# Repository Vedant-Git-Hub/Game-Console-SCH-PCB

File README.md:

# Game-Console-SCH-PCB
This repository consist of schematics and PCB for the game console hardware. THis project is designed and developed in KICAD-5.

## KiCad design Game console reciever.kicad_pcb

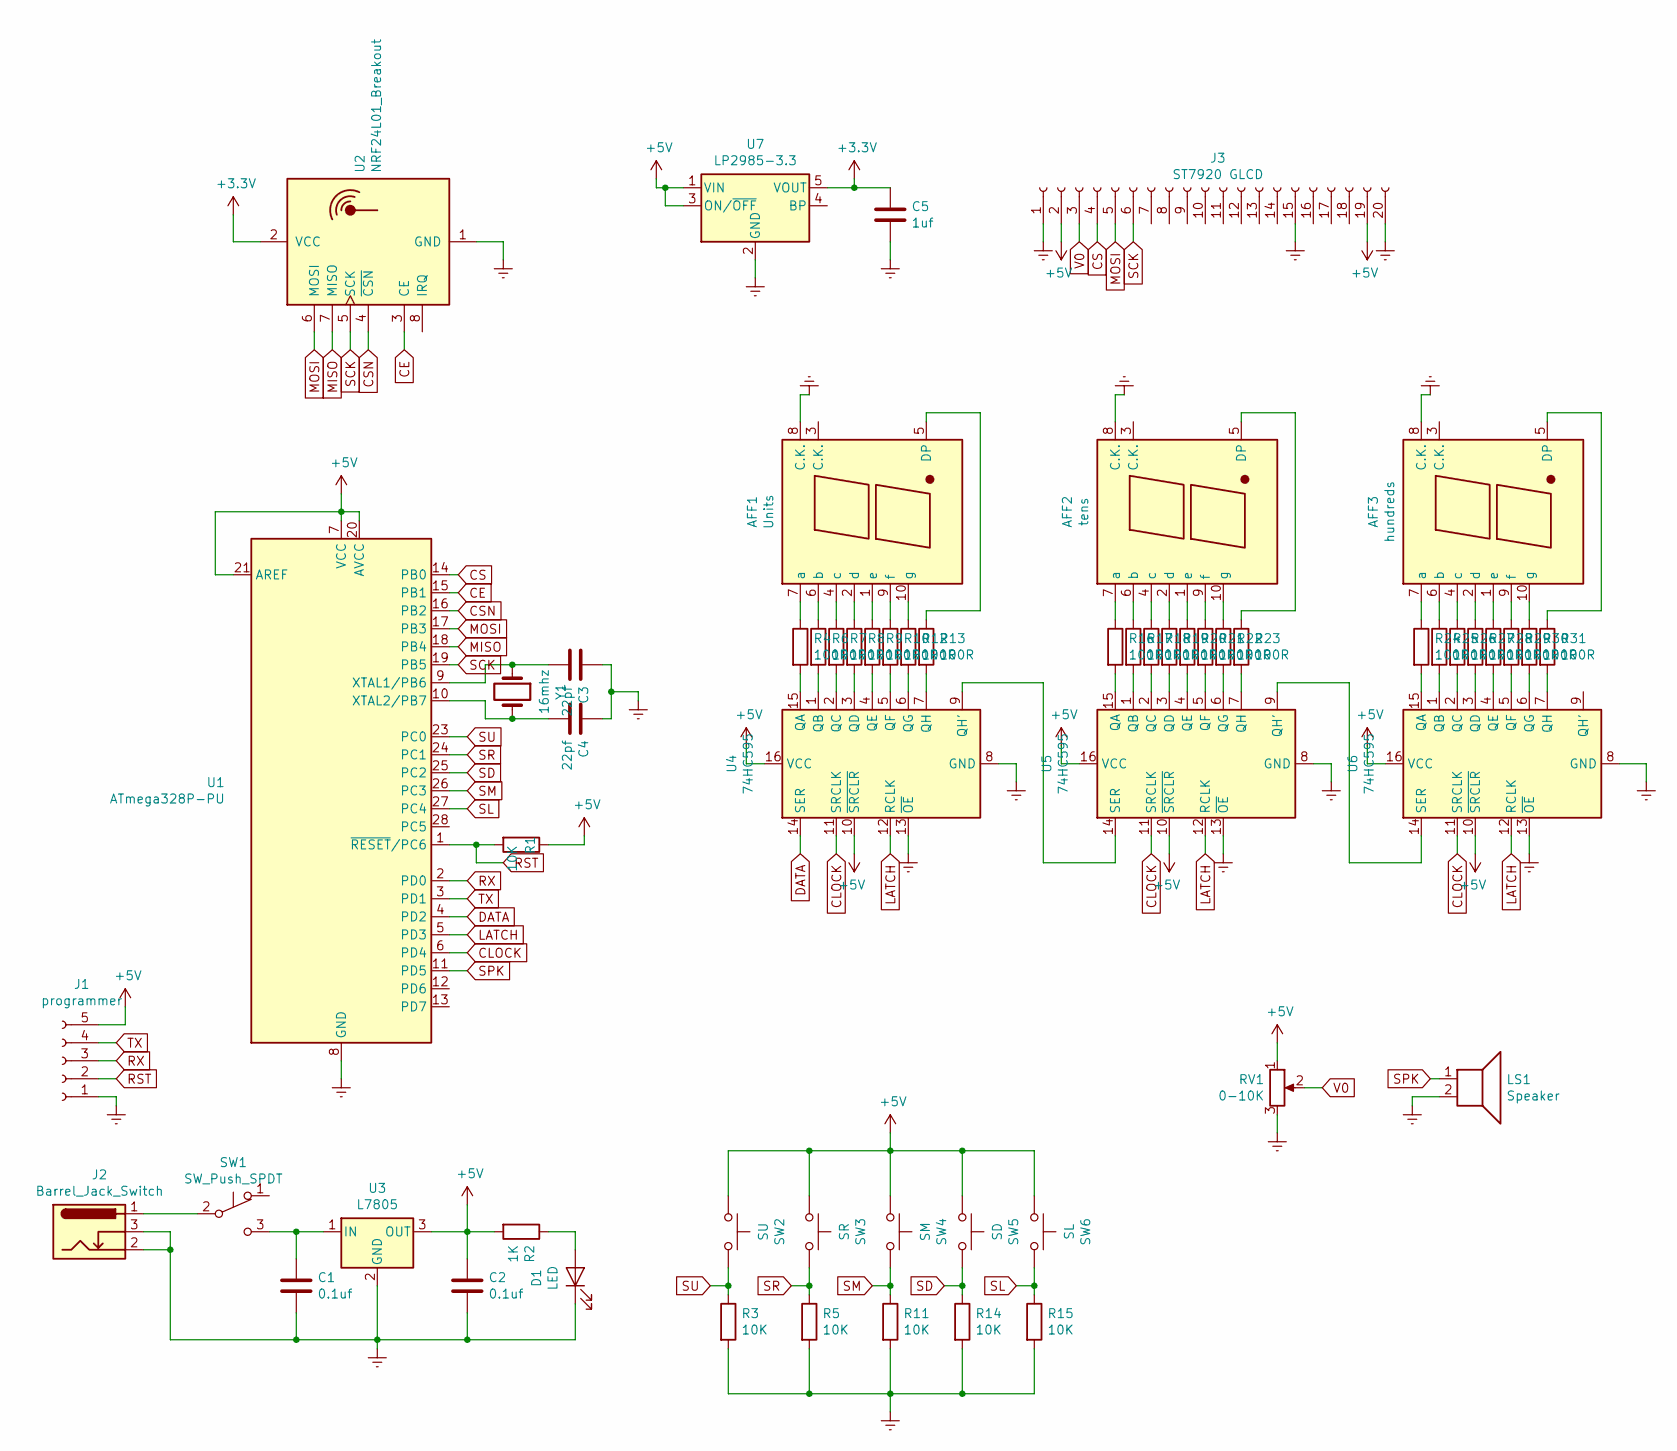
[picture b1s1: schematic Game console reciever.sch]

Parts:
AFF1: Units; 7SegmentLED_LTS6760_LTS6780
AFF2: tens; 7SegmentLED_LTS6760_LTS6780
AFF3: hundreds; 7SegmentLED_LTS6760_LTS6780
C1, C2: 0.1uf; C_Disc_D5.0mm_W2.5mm_P5.00mm
C3, C4: 22pf; C_Disc_D5.0mm_W2.5mm_P5.00mm
C5: 1uf; C_Disc_D5.0mm_W2.5mm_P5.00mm
D1: LED; LED_D5.0mm
J1: programmer; PinHeader_1x05_P2.54mm_Vertical
J2: Barrel_Jack_Switch; BarrelJack_Wuerth_6941xx301002
J3: ST7920 GLCD; PinHeader_1x20_P2.54mm_Vertical
LS1: Speaker; PinHeader_1x02_P2.54mm_Vertical
R1, R3, R5, R11, R14, R15: 10K; R_Axial_DIN0207_L6.3mm_D2.5mm_P10.16mm_Horizontal
R2: 1K; R_Axial_DIN0207_L6.3mm_D2.5mm_P10.16mm_Horizontal
R4, R6, R7, R8, R9, R10, R12, R13, R16, R17, R18, R19, R20, R21, R22, R23, R24, R25, R26, R27, R28, R29, R30, R31: 100R; R_Axial_DIN0207_L6.3mm_D2.5mm_P10.16mm_Horizontal
RV1: 0-10K; Potentiometer_Bourns_3266Z_Horizontal
SW1: SW_Push_SPDT; PinHeader_1x03_P2.00mm_Vertical
SW2: SU; TE_FSM8JRT
SW3: SR; TE_FSM8JRT
SW4: SM; TE_FSM8JRT
SW5: SD; TE_FSM8JRT
SW6: SL; TE_FSM8JRT
U1: ATmega328P-PU; DIP-28_W7.62mm
U2: NRF24L01_Breakout; nRF24L01_Breakout
U3: L7805; TO254P460X1020X1945-3P
U4, U5, U6: 74HC595; DIP-16_W7.62mm_LongPads
U7: LP2985-3.3; SOT-23-5
Y1: 16mhz; Crystal_HC52-6mm_Vertical

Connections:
+3V3: C5.1, U2.2 (VCC), U7.5 (VOUT)
+5V: C2.1, J1.5, J3.2, J3.19, R1.1, R2.2, RV1.1, SW2.1, SW3.1, SW4.1, SW5.1, SW6.1, U1.7 (VCC), U1.20 (AVCC), U1.21 (AREF), U3.3 (OUT), U4.10 (~SRCLR), U4.16 (VCC), U5.10 (~SRCLR), U5.16 (VCC), U6.10 (~SRCLR), U6.16 (VCC), U7.1 (VIN), U7.3 (ON/~OFF~)
CE: U1.15 (PB1), U2.3 (CE)
CLOCK: U1.6 (PD4), U4.11 (SRCLK), U5.11 (SRCLK), U6.11 (SRCLK)
CS: J3.4, U1.14 (PB0)
CSN: U1.16 (PB2), U2.4 (~CSN)
DATA: U1.4 (PD2), U4.14 (SER)
Earth: AFF1.8 (C.K.), AFF2.8 (C.K.), AFF3.8 (C.K.), C1.2, C2.2, C3.1, C4.1, C5.2, D1.1 (K), J1.1, J2.2, J2.3, J3.1, J3.15, J3.20, LS1.2, R3.2, R5.2, R11.2, R14.2, R15.2, RV1.3, U1.8 (GND), U1.22 (GND), U2.1 (GND), U3.2 (GND), U4.8 (GND), U4.13 (~OE), U5.8 (GND), U5.13 (~OE), U6.8 (GND), U6.13 (~OE), U7.2 (GND)
LATCH: U1.5 (PD3), U4.12 (RCLK), U5.12 (RCLK), U6.12 (RCLK)
MISO: U1.18 (PB4), U2.7 (MISO)
MOSI: J3.5, U1.17 (PB3), U2.6 (MOSI)
unnamed: AFF1.1 (e), R9.1
unnamed: AFF1.2 (d), R8.1
unnamed: AFF1.4 (c), R7.1
unnamed: AFF1.5 (DP), R13.1
unnamed: AFF1.6 (b), R6.1
unnamed: AFF1.7 (a), R4.1
unnamed: AFF1.9 (f), R10.1
unnamed: AFF1.10 (g), R12.1
unnamed: AFF2.1 (e), R20.1
unnamed: AFF2.2 (d), R19.1
unnamed: AFF2.4 (c), R18.1
unnamed: AFF2.5 (DP), R23.1
unnamed: AFF2.6 (b), R17.1
unnamed: AFF2.7 (a), R16.1
unnamed: AFF2.9 (f), R21.1
unnamed: AFF2.10 (g), R22.1
unnamed: AFF3.1 (e), R28.1
unnamed: AFF3.2 (d), R27.1
unnamed: AFF3.4 (c), R26.1
unnamed: AFF3.5 (DP), R31.1
unnamed: AFF3.6 (b), R25.1
unnamed: AFF3.7 (a), R24.1
unnamed: AFF3.9 (f), R29.1
unnamed: AFF3.10 (g), R30.1
unnamed: C1.1, SW1.3 (C), U3.1 (IN)
unnamed: C3.2, U1.9 (XTAL1/PB6), Y1.1
unnamed: C4.2, U1.10 (XTAL2/PB7), Y1.2
unnamed: D1.2 (A), R2.1
unnamed: J2.1, SW1.2 (B)
unnamed: R4.2, U4.15 (QA)
unnamed: R6.2, U4.1 (QB)
unnamed: R7.2, U4.2 (QC)
unnamed: R8.2, U4.3 (QD)
unnamed: R9.2, U4.4 (QE)
unnamed: R10.2, U4.5 (QF)
unnamed: R12.2, U4.6 (QG)
unnamed: R13.2, U4.7 (QH)
unnamed: R16.2, U5.15 (QA)
unnamed: R17.2, U5.1 (QB)
unnamed: R18.2, U5.2 (QC)
unnamed: R19.2, U5.3 (QD)
unnamed: R20.2, U5.4 (QE)
unnamed: R21.2, U5.5 (QF)
unnamed: R22.2, U5.6 (QG)
unnamed: R23.2, U5.7 (QH)
unnamed: R24.2, U6.15 (QA)
unnamed: R25.2, U6.1 (QB)
unnamed: R26.2, U6.2 (QC)
unnamed: R27.2, U6.3 (QD)
unnamed: R28.2, U6.4 (QE)
unnamed: R29.2, U6.5 (QF)
unnamed: R30.2, U6.6 (QG)
unnamed: R31.2, U6.7 (QH)
unnamed: U4.9 (QH'), U5.14 (SER)
unnamed: U5.9 (QH'), U6.14 (SER)
RST: J1.2, R1.2, U1.1 (~RESET~/PC6)
RX: J1.3, U1.2 (PD0)
SCK: J3.6, U1.19 (PB5), U2.5 (SCK)
SD: R14.1, SW5.2, U1.25 (PC2)
SL: R15.1, SW6.2, U1.27 (PC4)
SM: R11.1, SW4.2, U1.26 (PC3)
SPK: LS1.1, U1.11 (PD5)
SR: R5.1, SW3.2, U1.24 (PC1)
SU: R3.1, SW2.2, U1.23 (PC0)
TX: J1.4, U1.3 (PD1)
V0: J3.3, RV1.2

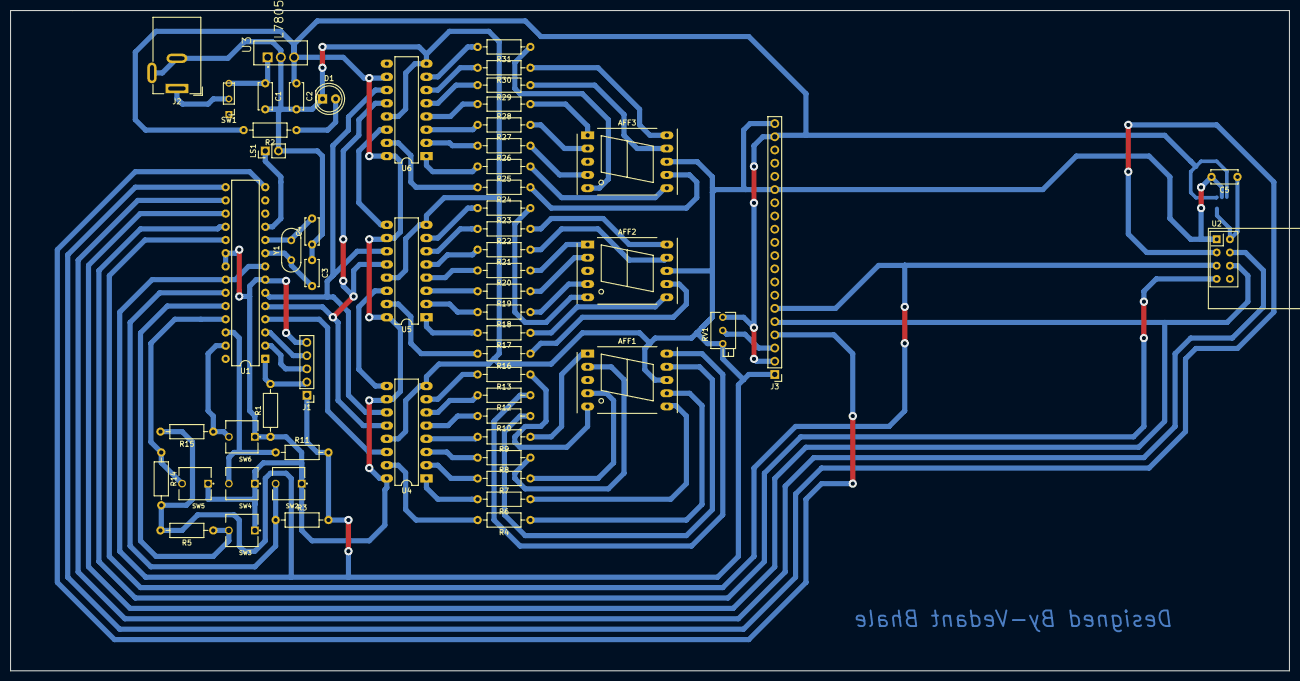
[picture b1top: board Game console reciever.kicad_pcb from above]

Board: 2 copper layers, 246.0 x 127.0 mm, 59 parts (1 on the bottom side), 77 nets.

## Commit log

2024-07-23 First commit to this repository to add files.
